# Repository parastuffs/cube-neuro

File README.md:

# Early Curiosity - Cube

This is the documentation for the **third version** of the cube. v1 is available [here](https://github.com/parastuffs/cube-neuro/blob/main/README_V1.md) and v2 [here](https://github.com/parastuffs/cube-neuro/blob/main/README_V2.md).
Pictures of the development are available [online](https://photos.app.goo.gl/61a8nF2CPd1NJpt47)(v2 [here](https://photos.app.goo.gl/r4oXzCXrc1rNYwXG9)).

The cube has a button on five of its faces, and a hatch on the bottom face.
Under the hatch, there is:
- A USB-C port for programming and battery charging. 
> [!IMPORTANT]  
> To charge the battery, the cube needs to be **on**.
- A switch to turn the cube on and off.
- A micro-SD reader.

In the demonstration mode, pressing a button might trigger a sound depending on the cube configuration.
> [!IMPORTANT]
> To switch to experiment mode, you need to keep any of the buttons pressed for two seconds.
In order to come back to demonstration mode, you need to reboot the cube by turning it off and on again.

In experiment mode, pressing a button never triggers a sound, but all events are saved to the SD card in a `.csv` file. It follows this structure:

| observation | face | pression_start | pression_stop | sound | isExperiment |
| --- | --- | --- | --- | --- | --- |
| Observation count, incremental | 1 to 5 value of the pressed button | Time of start of press | Time of end of press | Sound played (1) or not (0) | Press durring demo (0) or experiment (1) |

Time measurement is in milliseconds, 0 being the powering up of the cube.

### Change the sound played during demonstration mode
The sound must be located at the root of the micro-SD card and **must** be named `sound.mp3`.

### The cube and dates
The micro-controller does not have any notion of the actual date. With each reboot, it starts couting time from zero again. All files are thus created with an erroneous creation date which should be ignored.

### File structure
Upon starting for the first time, the micro-controller checks if the file `exp_id.txt` exists and does create it if it's not found.
This file contains a list of all incremental IDs of previously saved experiments.
When the cube switches to experiment mode, the micro-controller checks the last ID in that file, increment it, and create a new experiment ID.
This number `<id>` is then used to create a file `exp_<id>.csv`.

Just like audio file, experiment file names are not case sensitive (`EXP_20.csv` is the same as `exp_20.csv`) and cannot exceed eight characters without the file extension (`exp_20.csv` is valid, `experience_20.csv` or `exp_12345.csv` are not).

### Update the cube configuration
In their default configuration, the cube behave as such in demonstration mode:
- Alpha: Always play sound
- Beta: No sound
- Gamma: Sound / No sound
- Delta: No sound x7 / Sound

A more detailed guide is available [here](https://github.com/parastuffs/cube-neuro/tree/main/code) on updating the code.

### Hardware
This [file](https://github.com/parastuffs/cube-neuro/blob/main/BOM.md) has a full bill of materials. Since v3, the cube is laser cutted instead of 3D printed.

### Improvement considered
- Add an RTC to keep track of time.
- Having a configuration file for the cube type.

Copyright © 2026 Quentin Delhaye, Romain di Stasi, Claire Kabdebon, Adélaïde de Heering.

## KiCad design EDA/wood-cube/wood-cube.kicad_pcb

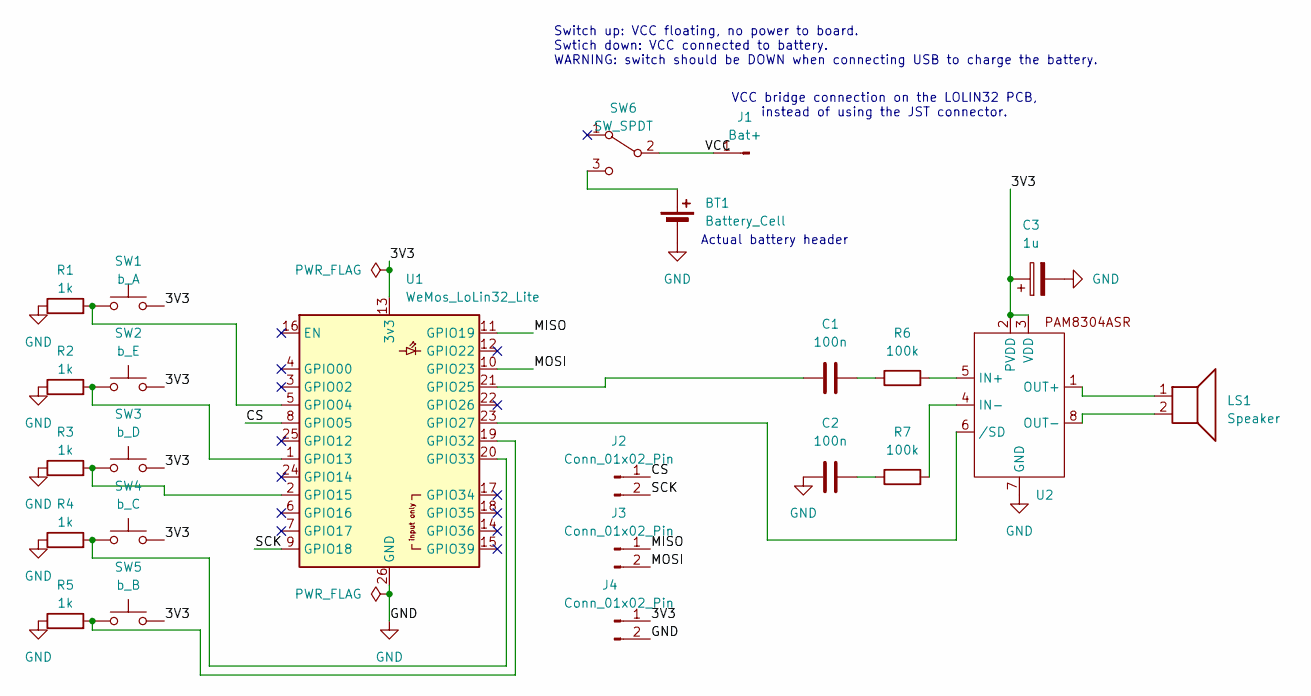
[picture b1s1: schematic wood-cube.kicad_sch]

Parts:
BT1: Battery_Cell; PinHeader_1x02_P1.27mm_Vertical
C1, C2: 100n; C_1206_3216Metric_Pad1.33x1.80mm_HandSolder
C3: 1u; CP_Elec_4x3.9
J1: Bat+; PinHeader_1x01_P2.54mm_Vertical
J2, J3, J4: Conn_01x02_Pin; PinHeader_1x02_P2.54mm_Vertical
LS1: Speaker; PinHeader_1x02_P1.27mm_Vertical
R1, R2, R3, R4, R5: 1k; R_1206_3216Metric_Pad1.30x1.75mm_HandSolder
R6, R7: 100k; R_1206_3216Metric_Pad1.30x1.75mm_HandSolder
SW1: b_A; PinHeader_1x02_P2.54mm_Vertical
SW2: b_E; PinHeader_1x02_P2.54mm_Vertical
SW3: b_D; PinHeader_1x02_P2.54mm_Vertical
SW4: b_C; PinHeader_1x02_P2.54mm_Vertical
SW5: b_B; PinHeader_1x02_P2.54mm_Vertical
SW6: SW_SPDT; SW_Slide_SPDT_Angled_CK_OS102011MA1Q
U1: WeMos_LoLin32_Lite; WEMOS_LoLin32_Lite
U2: MSOP-8_3x3mm_P0.65mm

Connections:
/3V3: C3.1, J4.1, SW1.2, SW2.2, SW3.2, SW4.2, SW5.2, U1.13 (3v3), U2.2 (PVDD), U2.3 (VDD)
/CS: J2.1, U1.8 (GPIO05)
/MISO: J3.1, U1.11 (GPIO19)
/MOSI: J3.2, U1.10 (GPIO23)
/SCK: J2.2, U1.9 (GPIO18)
/VCC: J1.1, SW6.2 (B)
GND: BT1.2 (-), C2.1, C3.2, J4.2, R1.1, R2.1, R3.1, R4.1, R5.1, U1.26 (GND), U2.7 (GND)
unnamed: BT1.1 (+), SW6.3 (C)
unnamed: C1.2, R6.1
unnamed: C2.2, R7.1
unnamed: R1.2, SW1.1, U1.5 (GPIO04)
unnamed: R2.2, SW2.1, U1.1 (GPIO13)
unnamed: R3.2, SW3.1, U1.2 (GPIO15)
unnamed: C1.1, U1.21 (GPIO25)
unnamed: U1.23 (GPIO27), U2.6 (/SD)
unnamed: R5.2, SW5.1, U1.19 (GPIO32)
unnamed: R4.2, SW4.1, U1.20 (GPIO33)
unnamed: R6.2, U2.5 (IN+)
unnamed: R7.2, U2.4 (IN-)
unnamed: LS1.1, U2.1 (OUT+)
unnamed: LS1.2, U2.8 (OUT-)

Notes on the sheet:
Actual battery header
Switch up: VCC floating, no power to board. Swtich down: VCC connected to battery. WARNING: switch should be DOWN when connecting USB to charge the battery.
VCC bridge connection on the LOLIN32 PCB, instead of using the JST connector.

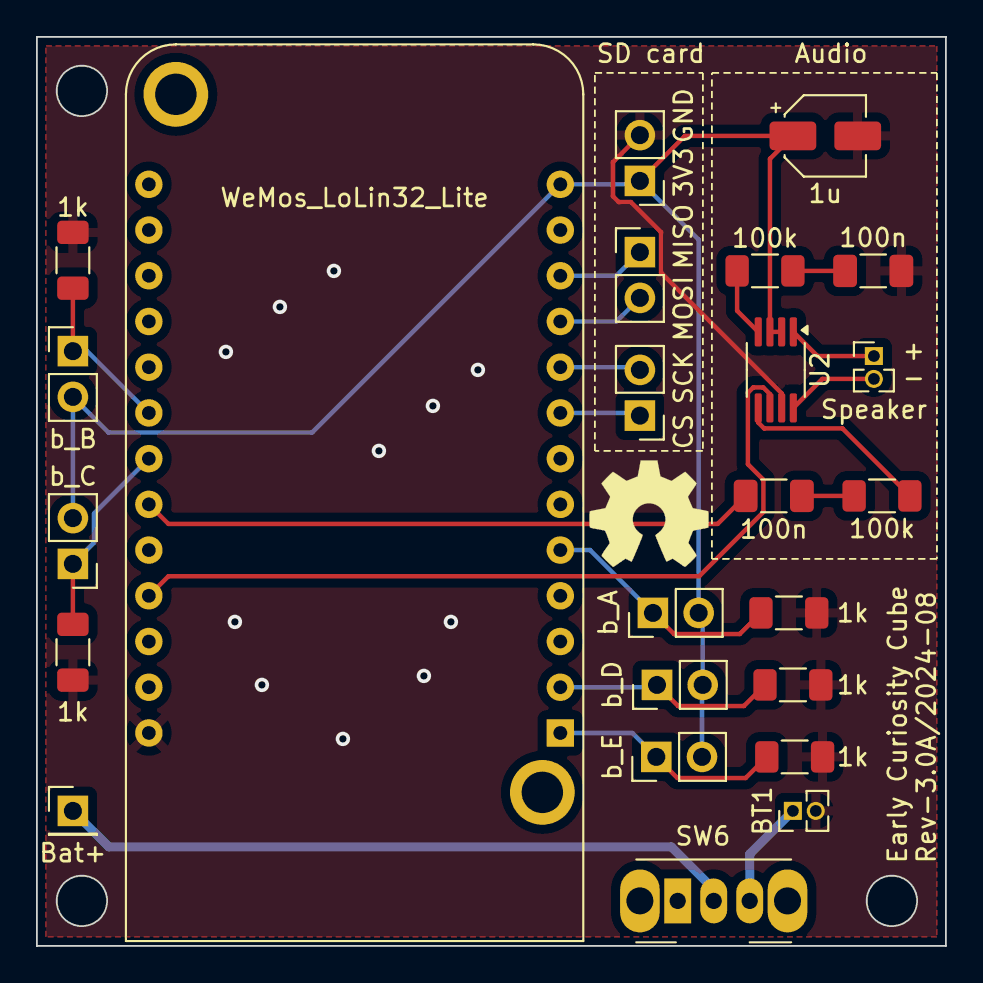
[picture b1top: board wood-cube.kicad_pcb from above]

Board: 2 copper layers, 50.5 x 50.5 mm, 24 parts (0 on the bottom side), 21 nets.

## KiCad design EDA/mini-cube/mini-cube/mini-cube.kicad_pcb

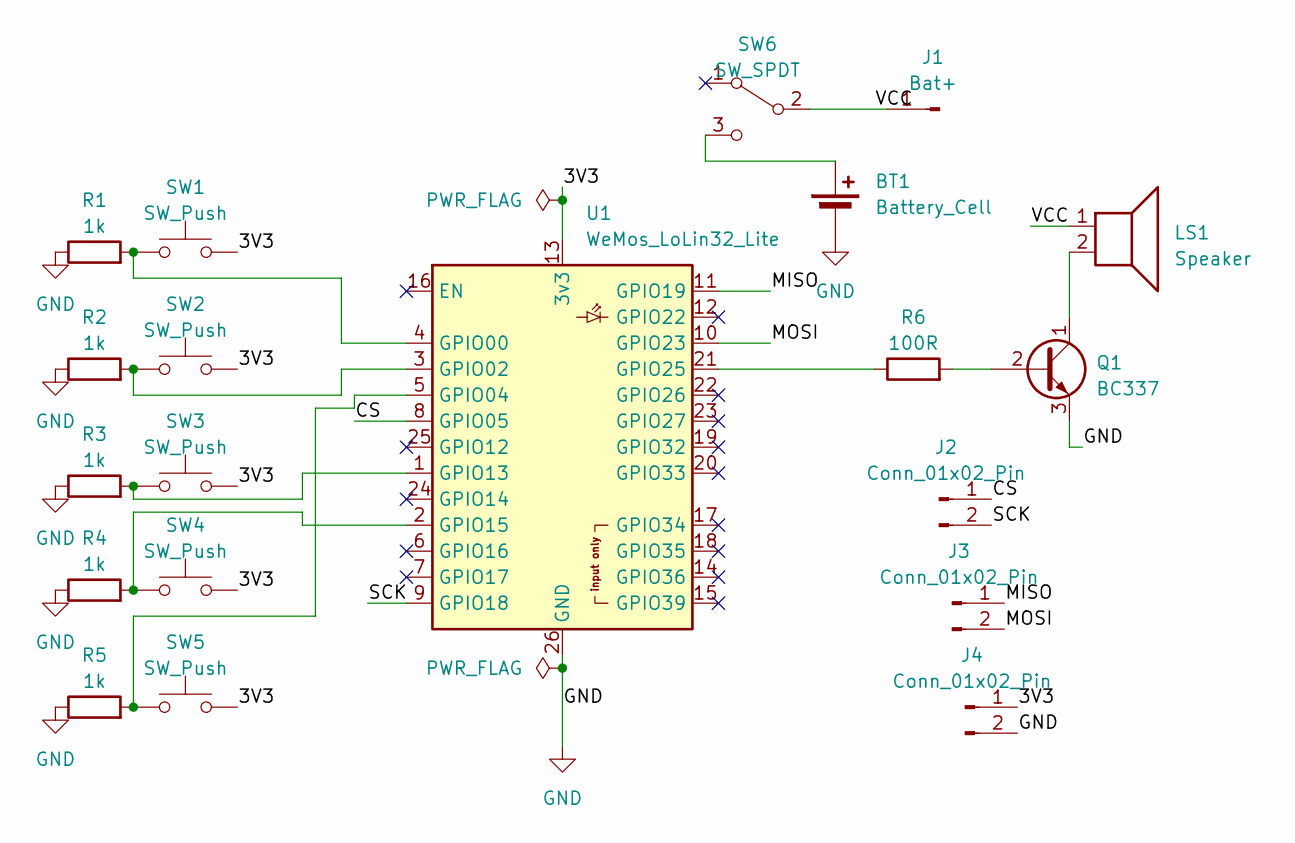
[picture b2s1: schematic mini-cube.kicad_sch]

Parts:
BT1: Battery_Cell; PinHeader_1x02_P1.27mm_Vertical
J1: Bat+; Pin_D1.0mm_L10.0mm
J2, J3, J4: Conn_01x02_Pin; PinHeader_1x02_P1.27mm_Vertical
LS1: Speaker; PinHeader_1x02_P1.27mm_Vertical
Q1: BC337; TO-92_Inline_Wide
R1, R2, R3, R4, R5: 1k; R_Axial_DIN0207_L6.3mm_D2.5mm_P2.54mm_Vertical
R6: 100R; R_Axial_DIN0207_L6.3mm_D2.5mm_P2.54mm_Vertical
SW1, SW2, SW3, SW4, SW5: SW_Push; PinHeader_1x02_P1.27mm_Vertical
SW6: SW_SPDT; SW_Slide_1P2T_CK_OS102011MS2Q
U1: WeMos_LoLin32_Lite; WEMOS_LoLin32_Lite

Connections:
/3V3: J4.1, SW1.2, SW2.2, SW3.2, SW4.2, SW5.2, U1.13 (3v3)
/CS: J2.1, U1.8 (GPIO05)
/MISO: J3.1, U1.11 (GPIO19)
/MOSI: J3.2, U1.10 (GPIO23)
/SCK: J2.2, U1.9 (GPIO18)
/VCC: J1.1, LS1.1, SW6.2 (B)
GND: J4.2, Q1.3 (E), R1.1, R2.1, R3.1, R4.1, R5.1, U1.26 (GND); also elsewhere on the board
unnamed 7: BT1.1 (+), SW6.3 (C); also elsewhere on the board
unnamed: Q1.2 (B), R6.2
unnamed: LS1.2, Q1.1 (C)
unnamed: R1.2, SW1.1, U1.4 (GPIO00)
unnamed: R2.2, SW2.1, U1.3 (GPIO02)
unnamed: R5.2, SW5.1, U1.5 (GPIO04)
unnamed: R3.2, SW3.1, U1.1 (GPIO13)
unnamed: R4.2, SW4.1, U1.2 (GPIO15)
unnamed: R6.1, U1.21 (GPIO25)

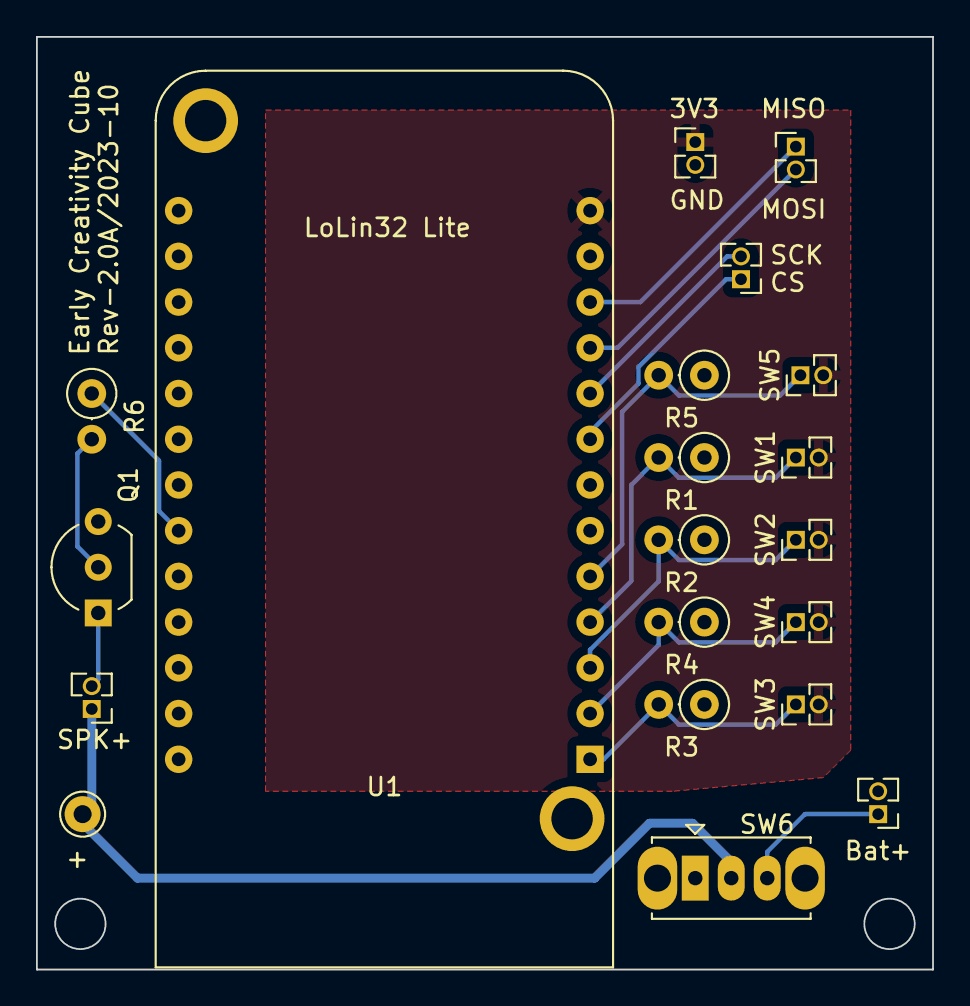
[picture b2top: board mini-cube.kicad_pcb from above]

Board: 2 copper layers, 49.8 x 51.8 mm, 20 parts (0 on the bottom side), 16 nets.

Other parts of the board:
Bat+: Battery_Cell; PinHeader_1x02_P1.27mm_Vertical

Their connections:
GND: Bat+.2 (-); also elsewhere on the board
unnamed 7: Bat+.1 (+); also elsewhere on the board

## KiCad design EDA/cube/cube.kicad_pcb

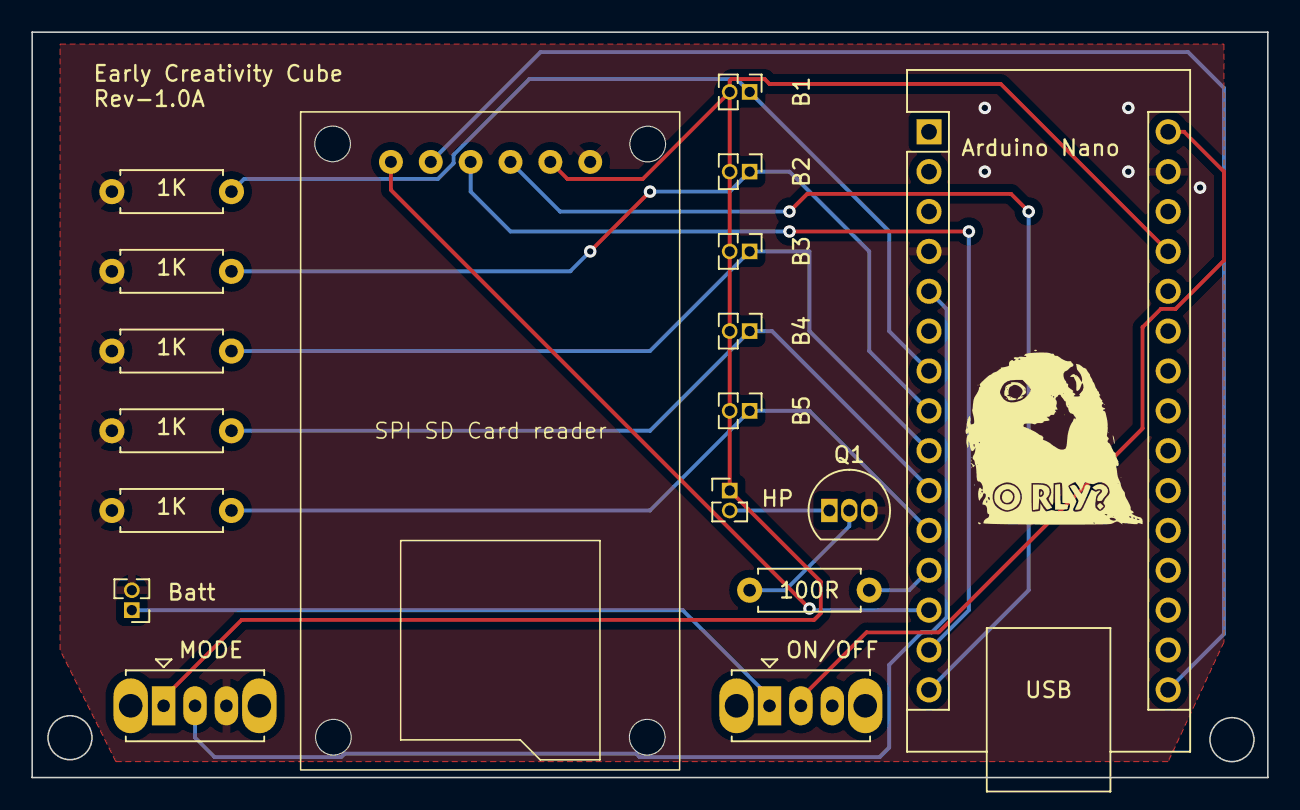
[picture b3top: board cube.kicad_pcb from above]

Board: 2 copper layers, 78.7 x 47.5 mm, 18 parts (0 on the bottom side), 17 nets.

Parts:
1K, 1K#2, 1K#3, 1K#4, 1K#5: 1k; R_Axial_DIN0207_L6.3mm_D2.5mm_P7.62mm_Horizontal
100R: 100R; R_Axial_DIN0207_L6.3mm_D2.5mm_P7.62mm_Horizontal
Arduino Nano: Arduino_Nano_Every; Arduino_Nano
B1, B2, B3, B4, B5: SW_Push; PinHeader_1x02_P1.27mm_Vertical
Batt: Battery_Cell; PinHeader_1x02_P1.27mm_Vertical
HP: Speaker; PinHeader_1x02_P1.27mm_Vertical
MODE: SW_SPDT; SW_Slide_1P2T_CK_OS102011MS2Q
ON/OFF: SW_SPDT; SW_Slide_1P2T_CK_OS102011MS2Q
Q1: BC337; TO-92_Inline
SPI SD Card reader: SD_AZDelivery

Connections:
/VCC: Arduino Nano.27 (+5V), B1.2, B2.2, B3.2, B4.2, B5.2, HP.1, MODE.1 (A), SPI SD Card reader.2 (VCC)
/Vin: Arduino Nano.30 (VIN), ON/OFF.2 (B)
GND: 1K.1, 1K#2.1, 1K#3.1, 1K#4.1, 1K#5.1, Arduino Nano.4 (GND), Arduino Nano.29 (GND), Batt.2 (-), MODE.3 (C), Q1.3 (E), SPI SD Card reader.1 (GND)
unnamed: Arduino Nano.5 (D2), MODE.2 (B)
unnamed: 1K#5.2, Arduino Nano.7 (D4), B1.1
unnamed: 1K.2, Arduino Nano.8 (D5), B2.1
unnamed: 1K#2.2, Arduino Nano.9 (D6), B3.1
unnamed: 1K#4.2, Arduino Nano.10 (D7), B4.1
unnamed: 1K#3.2, Arduino Nano.11 (D8), B5.1
unnamed: 100R.1, Arduino Nano.12 (D9)
unnamed: Arduino Nano.13 (D10), SPI SD Card reader.6 (CS)
unnamed: Arduino Nano.15 (MISO), SPI SD Card reader.3 (MISO)
unnamed: Arduino Nano.14 (MOSI), SPI SD Card reader.4 (MOSI)
unnamed: Arduino Nano.16 (SCK), SPI SD Card reader.5 (SCK)
unnamed: Batt.1 (+), ON/OFF.1 (A)
unnamed: 100R.2, Q1.2 (B)
unnamed: HP.2, Q1.1 (C)

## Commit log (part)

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2023-04-12 [EDA] Schematic
2023-04-12 [CAD] Cube FreeCAD file.
2023-04-12 [Code] First draft.
2023-04-12 [Code] Working prototype.
    - Checks the experiment number in a file.
    - Saves the measurements in a file.
    TODO:
    - Sound
    - Modes
2023-04-13 [Code] Sound and modes included.
2023-04-27 [Code] Updated demonstration and sound path. The played sound should be named 'sound.wav'.
2023-04-27 [EDA] PCB v1.0-revA
2023-04-27 [CAD] Cube v2 and STL
2023-04-28 [Doc] Update front documentation
2023-04-28 [Code] Comment buttons position.
2023-04-28 [images]
2023-04-28 [Doc] add images to readme
2023-04-28 [EDA] readme
2023-04-28 [Doc] bom
2023-04-28 [Doc] BOM Résistances et NPN
2023-04-28 [Doc] How to update the Arduino
2023-04-28 [Doc] Cubes configuration
2023-05-02 [Code] Update demo profiles
2023-05-02 [Doc] Update default configs
2024-03-09 [V2] Update BOM
2024-03-09 [V2] Son
2024-03-09 [V2] EDA
2024-03-09 [V2] Code and CAD
2024-03-09 [V2] BOM
2024-03-09 [V2] README
2024-03-09 [V2] Code README
2024-03-09 [V2] Link to photos
2024-10-20 [v3] Update main README for v3.
2024-10-20 [v3] Update cover image.
2024-10-20 [v3] EDA files for wood cube.
2024-10-20 [v3] CAD files for laser cutting v3.
2024-10-20 [v3] BOM update
2024-10-20 [v3] Code
2025-04-04 Code V3: increase experiment trigger up to 4 sec and avoid repeating sound trigger if a button is kept pressed.
2025-04-17 Update main_v3.ino
    Update of main_v3 with annotations – Romain di Stasi, version dated April 17th, 2025.
